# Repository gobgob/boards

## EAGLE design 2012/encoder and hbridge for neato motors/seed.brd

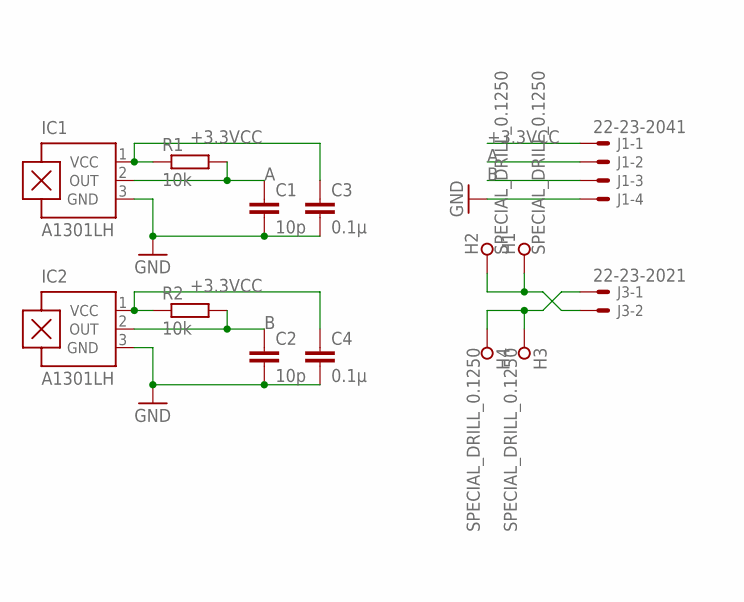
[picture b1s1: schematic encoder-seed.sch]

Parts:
C1, C2: 10p; C0805
C3, C4: 0.1µ; C0805
H1, H2, H3, H4: SPECIAL_DRILL_0.1250; PAD_0.1250
IC1, IC2: A1301LH; SOT23-W
J1: 22-23-2041
J3: 22-23-2021
R1, R2: 10k; R0805

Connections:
+3.3VCC: C3.1, C4.1, IC1.1 (VCC), IC2.1 (VCC), J1.1, R1.1, R2.1
A: C1.1, IC1.2 (OUT), J1.2, R1.2
B: C2.1, IC2.2 (OUT), J1.3, R2.2
GND: C1.2, C2.2, C3.2, C4.2, IC1.3 (GND), IC2.3 (GND), J1.4
unnamed: H3.1, H4.1, J3.1
unnamed: H1.1, H2.1, J3.2

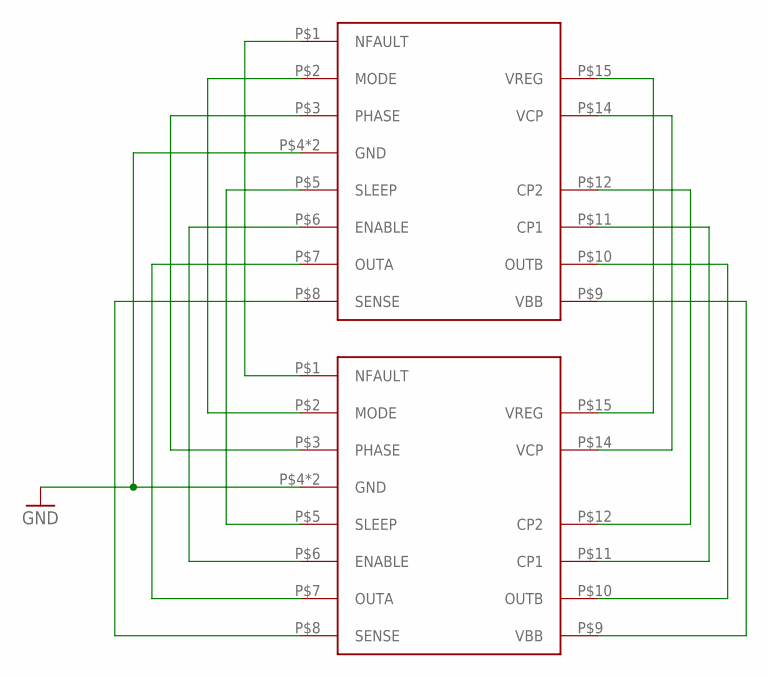
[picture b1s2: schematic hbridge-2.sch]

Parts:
U$1: A3950; 16TSSOP
U$2: A3950-DIL; DIL16

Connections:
GND1: U$1.P$4 (GND), U$1.P$13 (GND), U$2.P$4 (GND), U$2.P$13 (GND)
unnamed: U$1.P$1 (NFAULT), U$2.P$1 (NFAULT)
unnamed: U$1.P$2 (MODE), U$2.P$2 (MODE)
unnamed: U$1.P$3 (PHASE), U$2.P$3 (PHASE)
unnamed: U$1.P$6 (ENABLE), U$2.P$6 (ENABLE)
unnamed: U$1.P$7 (OUTA), U$2.P$7 (OUTA)
unnamed: U$1.P$5 (SLEEP), U$2.P$5 (SLEEP)
unnamed: U$1.P$8 (SENSE), U$2.P$8 (SENSE)
unnamed: U$1.P$15 (VREG), U$2.P$15 (VREG)
unnamed: U$1.P$14 (VCP), U$2.P$14 (VCP)
unnamed: U$1.P$12 (CP2), U$2.P$12 (CP2)
unnamed: U$1.P$11 (CP1), U$2.P$11 (CP1)
unnamed: U$1.P$10 (OUTB), U$2.P$10 (OUTB)
unnamed: U$1.P$9 (VBB), U$2.P$9 (VBB)

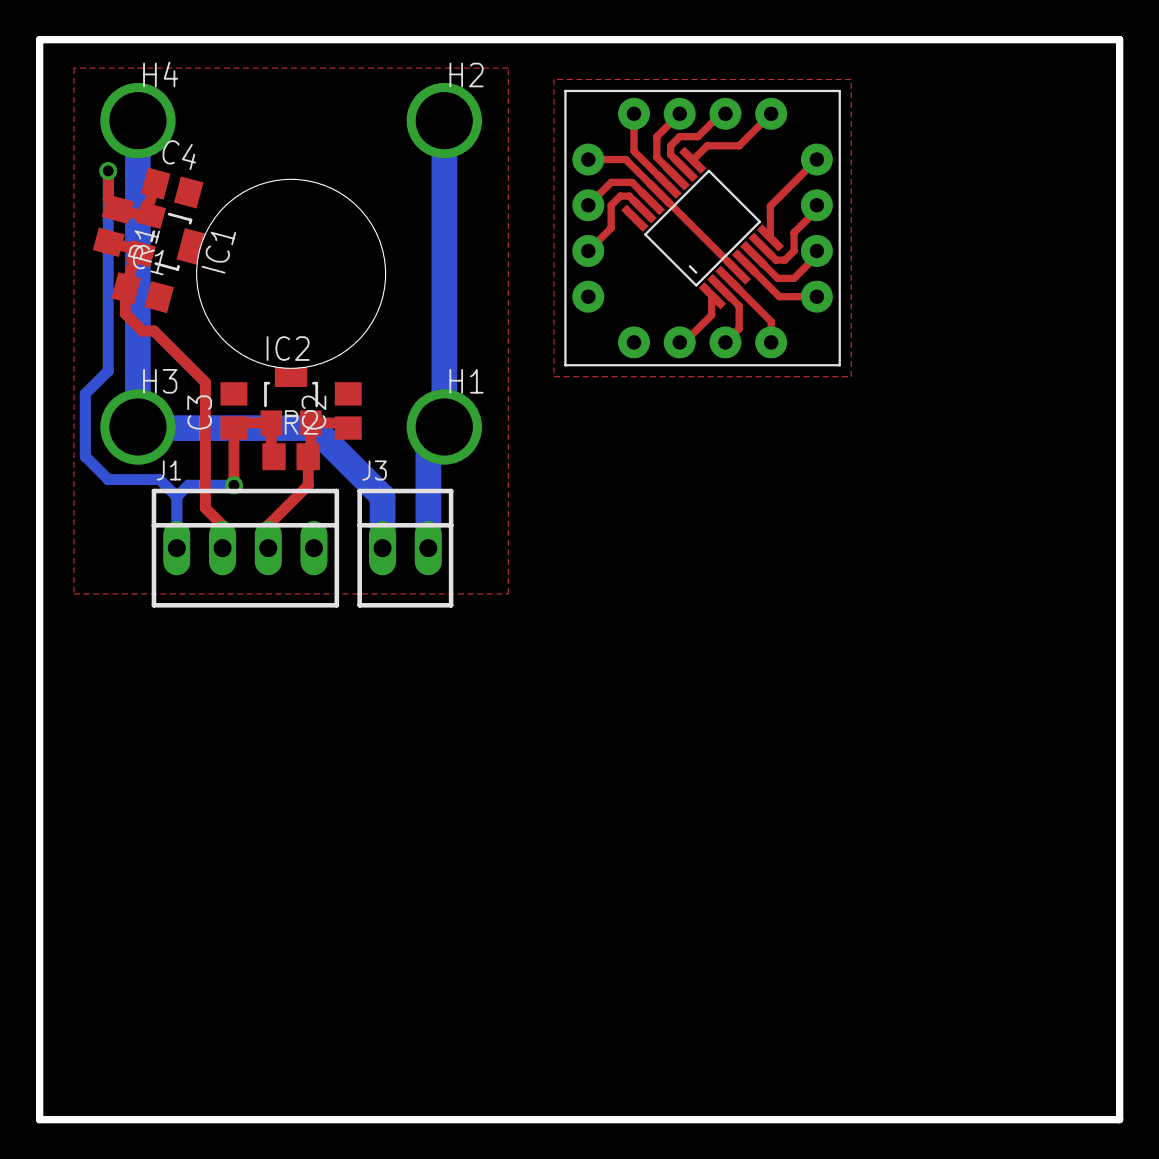
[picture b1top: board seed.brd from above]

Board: 2 copper layers, 60.0 x 60.0 mm, 16 parts (0 on the bottom side), 20 nets.

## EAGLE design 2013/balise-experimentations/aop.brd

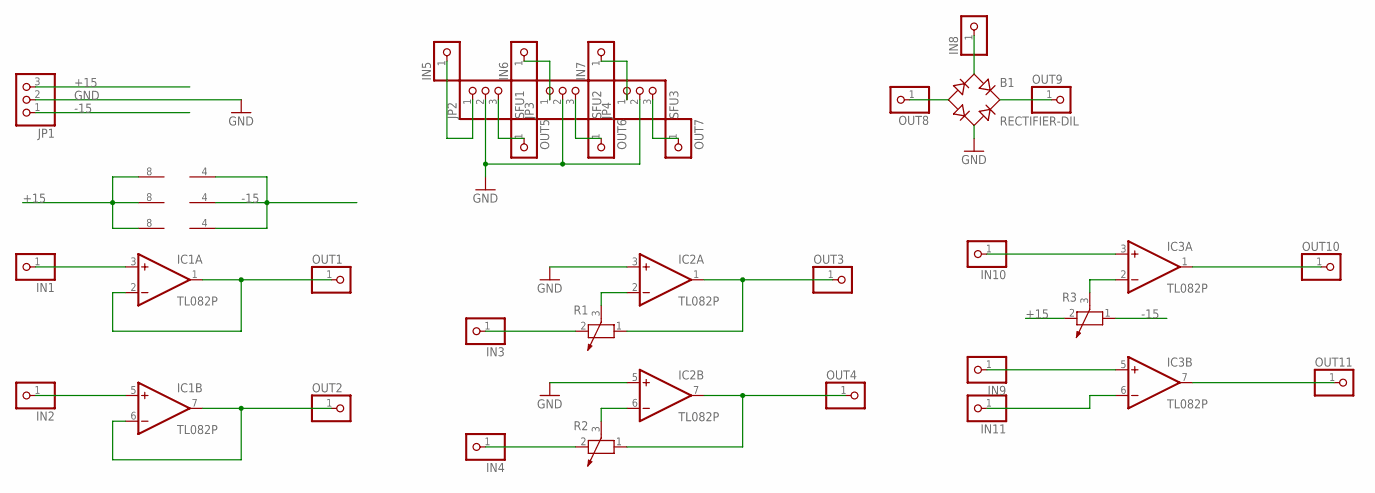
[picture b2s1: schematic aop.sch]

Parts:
B1: RECTIFIER-DIL; B-DIL
IC1, IC2, IC3: TL082P; DIL08
IN1, IN2, IN3, IN4, IN5, IN6, IN7, IN8, IN9, IN10, IN11: PINHD-1X1; 1X01
JP1: PINHD-1X3; 1X03
JP2: SFU1; 1X03
JP3: SFU2; 1X03
JP4: SFU3; 1X03
OUT1, OUT2, OUT3, OUT4, OUT5, OUT6, OUT7, OUT8, OUT9, OUT10, OUT11: PINHD-1X1; 1X01
R1, R2, R3: POTENTIOMETER_PT-10; PT-10

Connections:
+15: IC1.8 (V+), IC2.8 (V+), IC3.8 (V+), JP1.3, R3.2
-15: IC1.4 (V-), IC2.4 (V-), IC3.4 (V-), JP1.1, R3.1
GND: B1.AC2, IC2.3 (+IN), IC2.5 (+IN), JP1.2, JP2.2, JP3.2, JP4.2
unnamed: IC1.1 (OUT), IC1.2 (-IN), OUT1.1
unnamed: IC1.3 (+IN), IN1.1
unnamed: IC1.5 (+IN), IN2.1
unnamed: IC1.6 (-IN), IC1.7 (OUT), OUT2.1
unnamed: IC2.1 (OUT), OUT3.1, R1.1
unnamed: IC2.2 (-IN), R1.3
unnamed: IC2.7 (OUT), OUT4.1, R2.1
unnamed: IC2.6 (-IN), R2.3
unnamed: IN3.1, R1.2
unnamed: IN4.1, R2.2
unnamed: IN5.1, JP2.1
unnamed: JP2.3, OUT5.1
unnamed: IN6.1, JP3.1
unnamed: JP3.3, OUT6.1
unnamed: IN7.1, JP4.1
unnamed: JP4.3, OUT7.1
unnamed: B1.AC1, IN8.1
unnamed: IC3.1 (OUT), OUT10.1
unnamed: B1.-, OUT8.1
unnamed: B1.+, OUT9.1
unnamed: IC3.2 (-IN), R3.3
unnamed: IC3.7 (OUT), OUT11.1
unnamed: IC3.6 (-IN), IN11.1
unnamed: IC3.3 (+IN), IN10.1
unnamed: IC3.5 (+IN), IN9.1

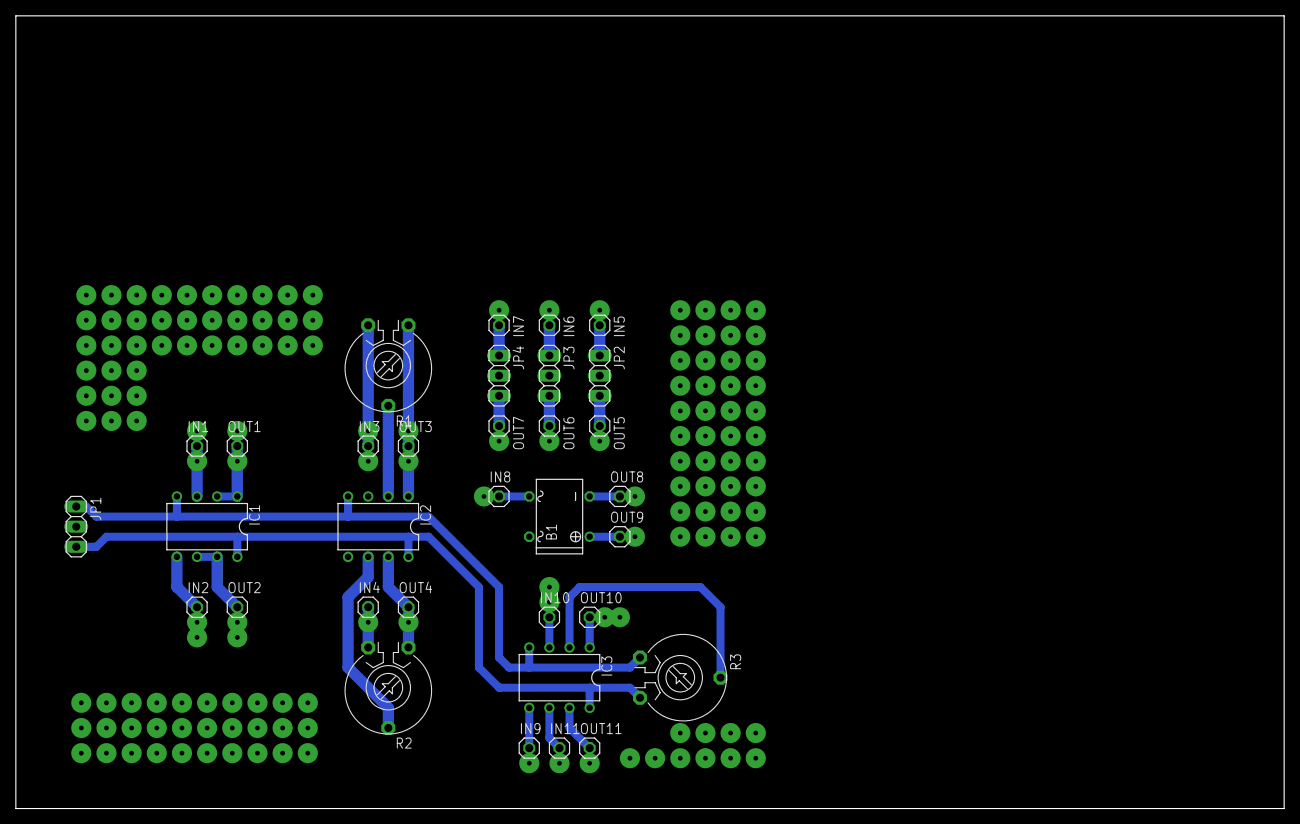
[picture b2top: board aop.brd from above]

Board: 2 copper layers, 160.0 x 100.0 mm, 33 parts (0 on the bottom side), 28 nets.

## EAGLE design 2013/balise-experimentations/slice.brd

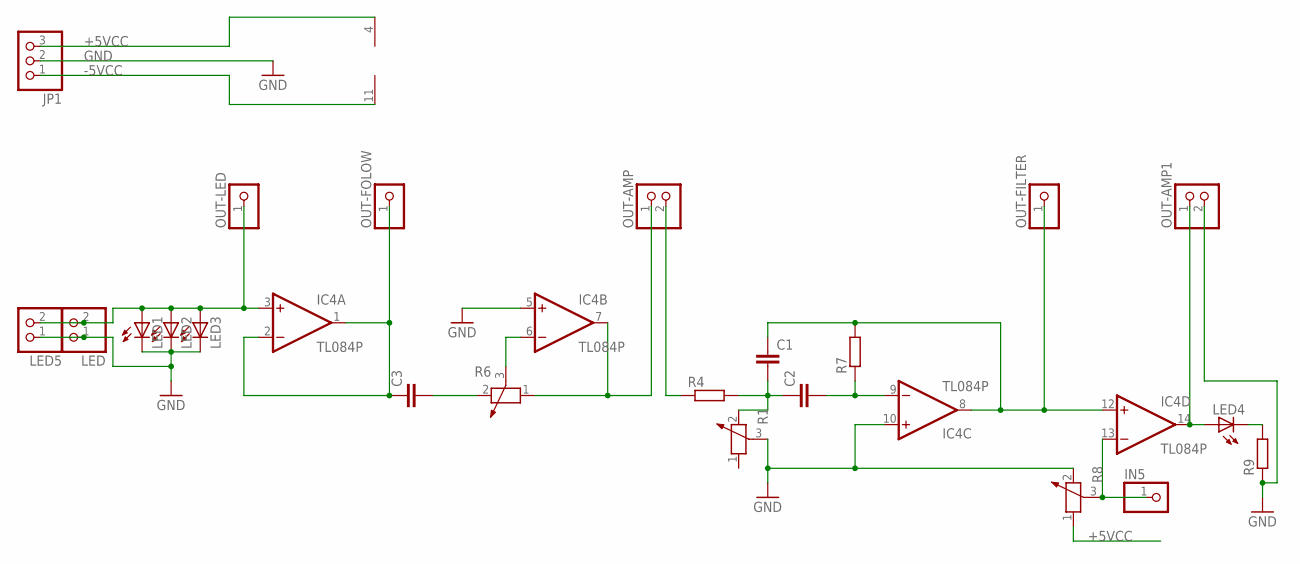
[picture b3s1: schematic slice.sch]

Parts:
C1, C2: C-EU150-064X183; C150-064X183
C3: C-EU050-024X044; C050-024X044
IC4: TL084P; DIL14
IN5: PINHD-1X1; 1X01
JP1: PINHD-1X3; 1X03
LED, LED5: PINHD-1X2; 1X02
LED1, LED2, LED3, LED4: LED5MM
OUT-AMP, OUT-AMP1: PINHD-1X2; 1X02
OUT-FILTER: PINHD-1X1; 1X01
OUT-FOLOW: PINHD-1X1; 1X01
OUT-LED: PINHD-1X1; 1X01
R1, R6, R8: POTENTIOMETER_PT-10; PT-10
R4, R7, R9: R-EU_0204/7; 0204/7

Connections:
+5VCC: IC4.4 (V+), JP1.3, R8.1
-5VCC: IC4.11 (V-), JP1.1
GND: IC4.5 (+IN), IC4.10 (+IN), JP1.2, LED.1, LED1.K (C), LED2.K (C), LED3.K (C), LED5.1, OUT-AMP1.2, R1.3, R8.2, R9.1
unnamed: OUT-AMP.2, R4.1
unnamed: C3.2, R6.2
unnamed: IC4.3 (+IN), LED.2, LED1.A, LED2.A, LED3.A, LED5.2, OUT-LED.1
unnamed: C3.1, IC4.1 (OUT), IC4.2 (-IN), OUT-FOLOW.1
unnamed: IC4.6 (-IN), R6.3
unnamed: IC4.7 (OUT), OUT-AMP.1, R6.1
unnamed: C1.2, C2.1, R1.2, R4.2
unnamed: C1.1, IC4.8 (OUT), IC4.12 (+IN), OUT-FILTER.1, R7.2
unnamed: C2.2, IC4.9 (-IN), R7.1
unnamed: IC4.13 (-IN), IN5.1, R8.3
unnamed: IC4.14 (OUT), LED4.A, OUT-AMP1.1
unnamed: LED4.K (C), R9.2

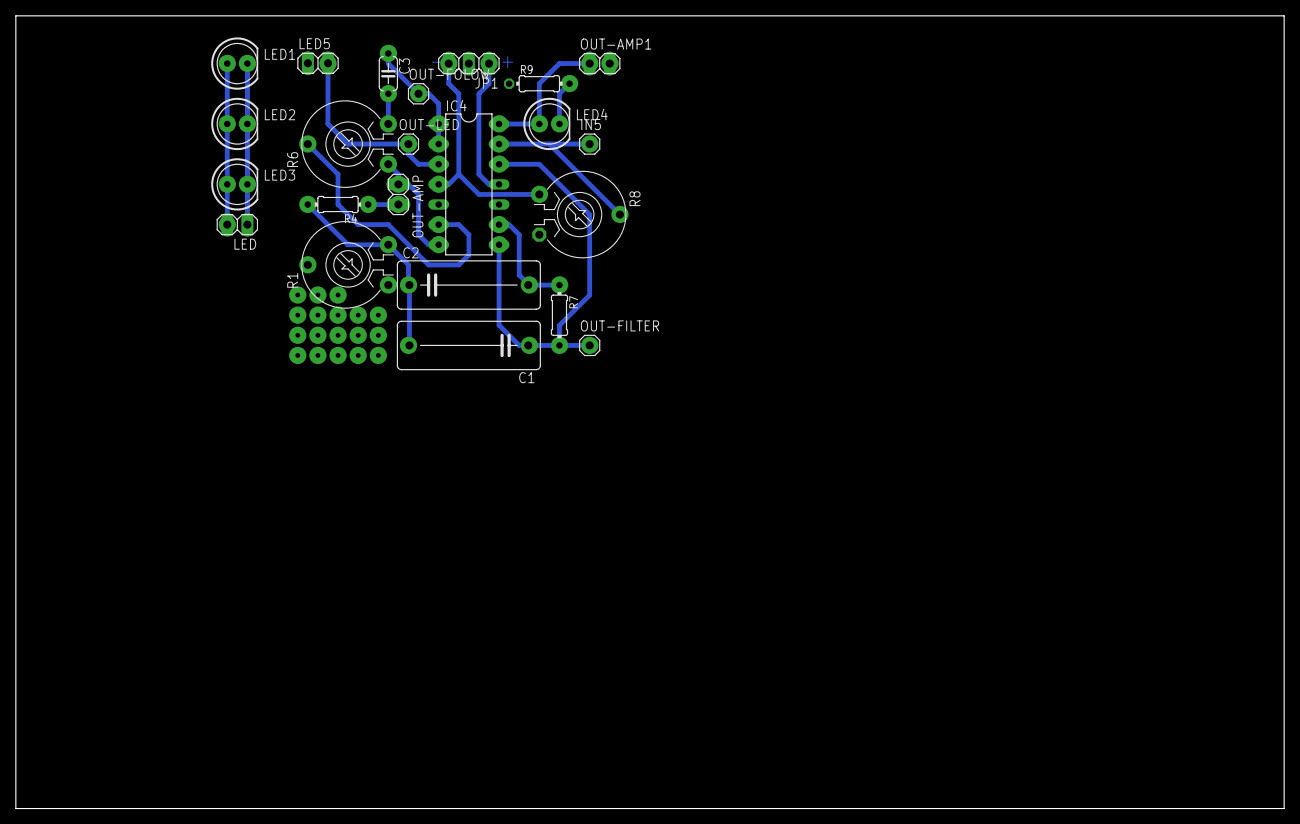
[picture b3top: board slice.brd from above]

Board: 2 copper layers, 160.0 x 100.0 mm, 23 parts (0 on the bottom side), 15 nets.

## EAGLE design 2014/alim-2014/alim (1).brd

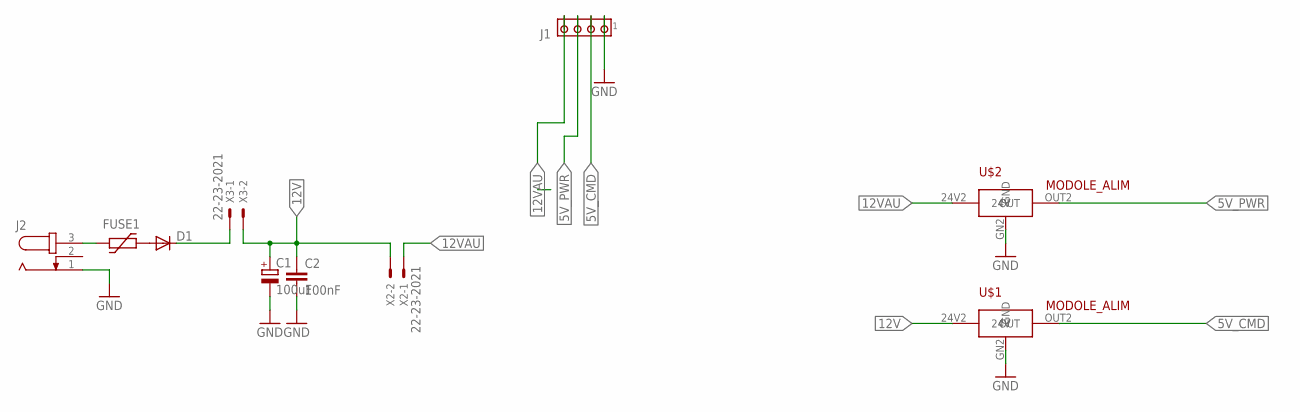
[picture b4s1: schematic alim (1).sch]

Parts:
C1: 100uF; E2,5-7
C2: 100nF; C050-035X075
D1: DIODE-DO07; DO07
FUSE1: MINI_SMD_C
J1: MTA04-100; 10X04MTA
J2: JACK-PLUG1; SPC4078
U$1, U$2: MODOLE_ALIM; PETITE_ALIM
X2, X3: 22-23-2021

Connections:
5V_CMD: J1.2, U$1.OUT2 (OUT)
5V_PWR: J1.3, U$2.OUT2 (OUT)
12V: C1.+, C2.1, U$1.24V2 (24V), X2.2, X3.2
12VAU: J1.4, U$2.24V2 (24V), X2.1
GND: C1.-, C2.2, J1.1, J2.1, U$1.GN2 (GND), U$2.GN2 (GND)
unnamed: D1.C, X3.1
unnamed: FUSE1.P$1 (1), J2.3
unnamed: D1.A, FUSE1.P$2 (2)

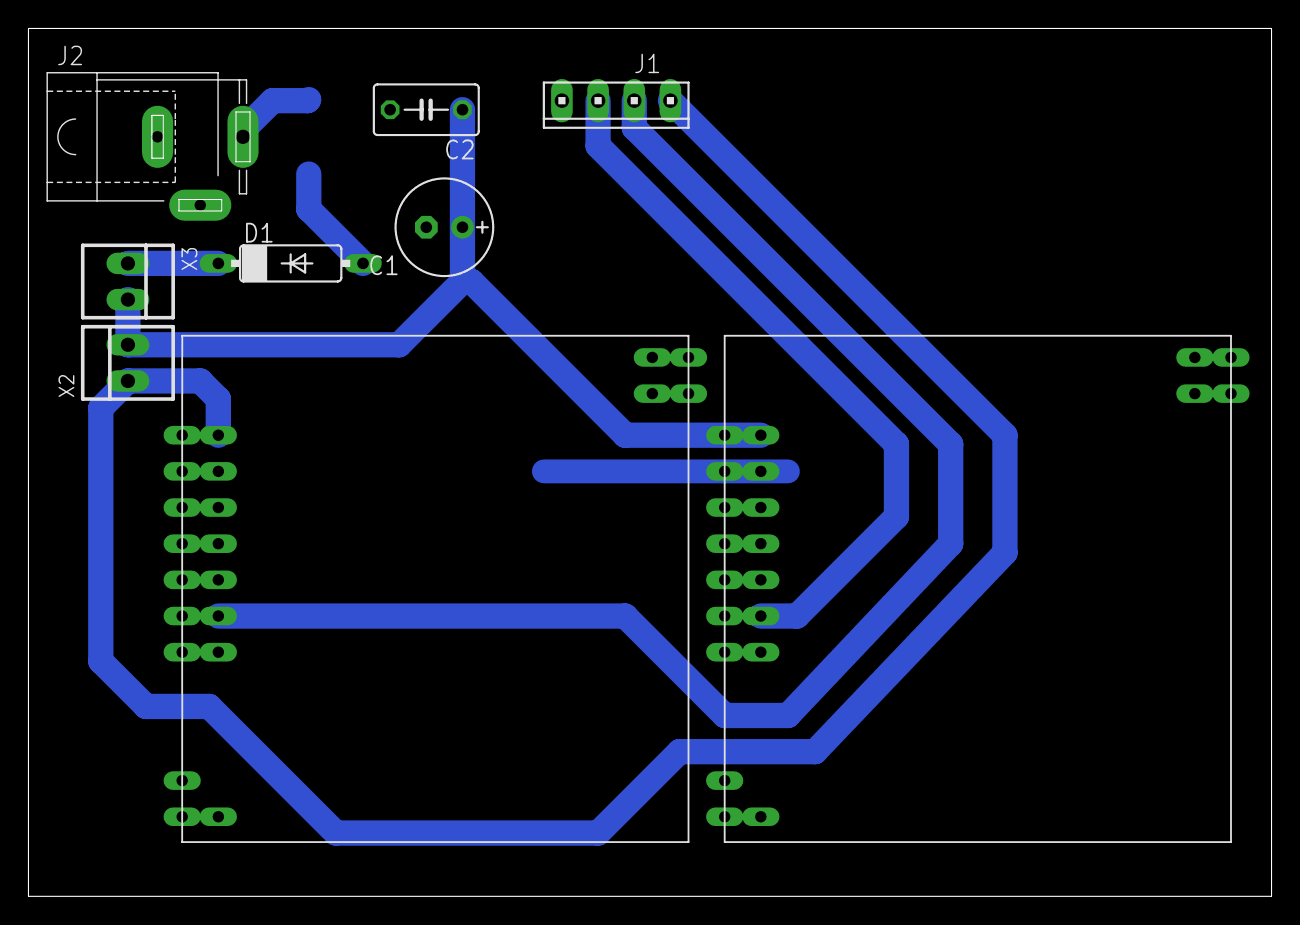
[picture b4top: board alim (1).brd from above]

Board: 2 copper layers, 87.3 x 61.0 mm, 10 parts (1 on the bottom side), 8 nets.

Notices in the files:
parts and their libraries:
raspberry: This library stands under the CERN Open Hardware Licence.
